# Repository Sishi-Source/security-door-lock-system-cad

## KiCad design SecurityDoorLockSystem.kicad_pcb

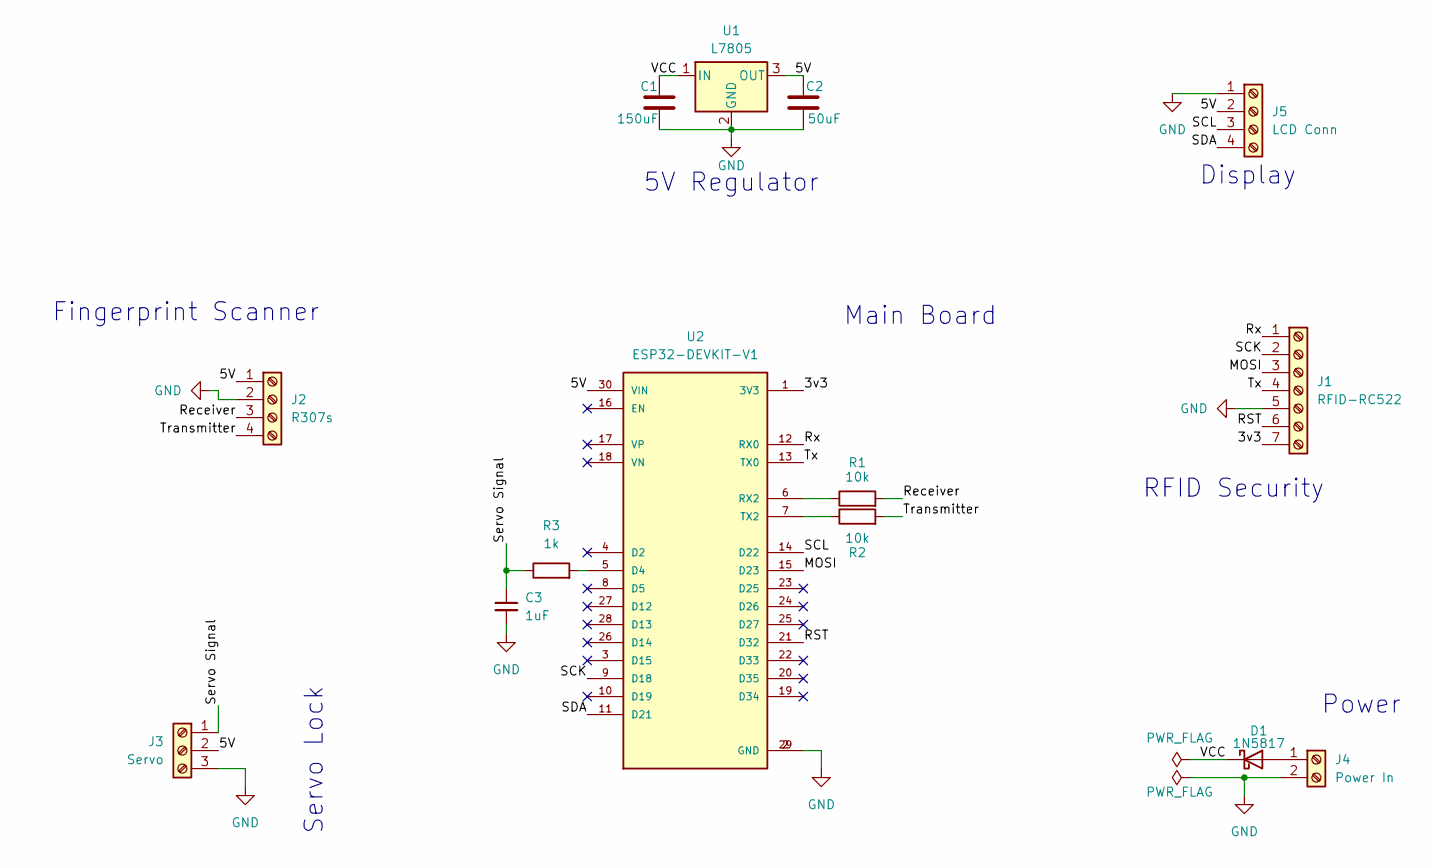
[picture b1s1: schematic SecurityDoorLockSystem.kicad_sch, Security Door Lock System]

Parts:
C1: 150uF; C_Radial_D5.0mm_H7.0mm_P2.00mm
C2: 50uF; C_Radial_D5.0mm_H7.0mm_P2.00mm
C3: 1uF; C_Radial_D5.0mm_H11.0mm_P2.00mm
D1: 1N5817; D_DO-41_SOD81_P7.62mm_Horizontal
J1: RFID-RC522; TerminalBlock_Phoenix_MKDS-1,5-7_1x07_P5.00mm_Horizontal
J2: R307s; TerminalBlock_Phoenix_MKDS-1,5-4_1x04_P5.00mm_Horizontal
J3: Servo; TerminalBlock_Phoenix_MKDS-1,5-3_1x03_P5.00mm_Horizontal
J4: Power In; TerminalBlock_Phoenix_MKDS-1,5-2_1x02_P5.00mm_Horizontal
J5: LCD Conn; TerminalBlock_Phoenix_MKDS-1,5-4_1x04_P5.00mm_Horizontal
R1, R2: 10k; R_Axial_DIN0207_L6.3mm_D2.5mm_P7.62mm_Horizontal
R3: 1k; R_Axial_DIN0207_L6.3mm_D2.5mm_P7.62mm_Horizontal
U1: L7805; TO-220-3_Horizontal_TabDown
U2: ESP32-DEVKIT-V1; MODULE_ESP32_DEVKIT_V1; PARTREV N/A

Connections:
/3v3: J1.7, U2.1 (3V3)
/5V: C2.1, J2.1, J3.2, J5.2, U1.3 (OUT), U2.30 (VIN)
/MOSI: J1.3, U2.15 (D23)
/RST: J1.6, U2.21 (D32)
/Receiver: J2.3, R1.2
/Rx: J1.1, U2.12 (RX0)
/SCK: J1.2, U2.9 (D18)
/SCL: J5.3, U2.14 (D22)
/SDA: J5.4, U2.11 (D21)
/Servo Signal: C3.1, J3.1, R3.1
/Transmitter: J2.4, R2.2
/Tx: J1.4, U2.13 (TX0)
/VCC: C1.1, D1.1 (K), U1.1 (IN)
GND: C1.2, C2.2, C3.2, J1.5, J2.2, J3.3, J4.2, J5.1, U1.2 (GND), U2.2 (GND), U2.29 (GND)
unnamed: D1.2 (A), J4.1
unnamed: R3.2, U2.5 (D4)
unnamed: R1.1, U2.6 (RX2)
unnamed: R2.1, U2.7 (TX2)

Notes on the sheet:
Power
Main Board
Display
RFID Security
Servo Lock
Fingerprint Scanner
5V Regulator

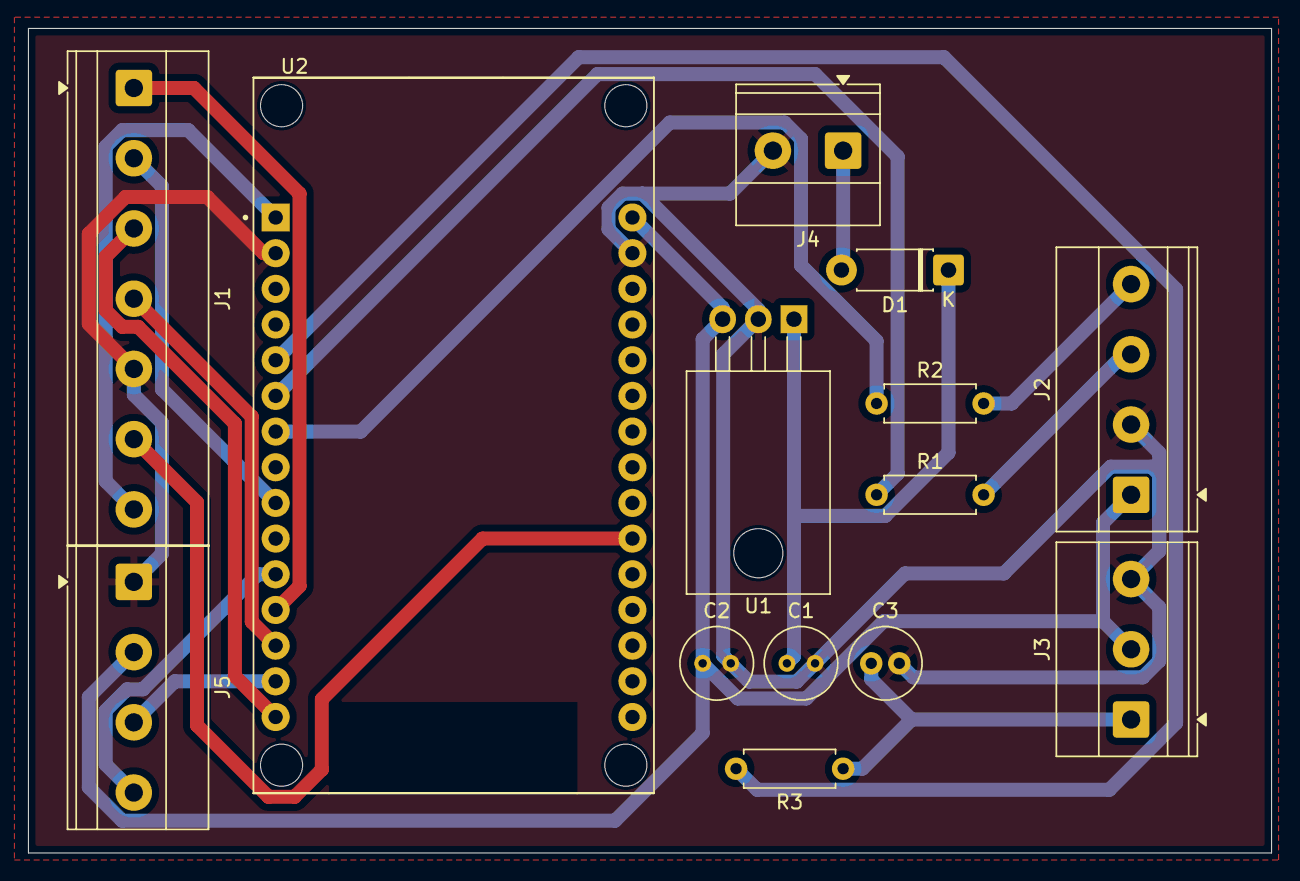
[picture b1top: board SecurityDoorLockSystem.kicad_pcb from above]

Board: 2 copper layers, 88.5 x 58.7 mm, 14 parts (0 on the bottom side), 18 nets.

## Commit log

2025-09-27 version 1
2025-09-28 version 2
    increased track width
    added voltage regulator
    corrected tht-friendly error
2025-09-28 version 2
    updated gerber plot files
    updated pdf plot files
    updated gerber/pdf drill maps files
2025-10-01 updated backup
2025-10-01 added: protection -- modified: pcb, schematic
    added power source polarity protection
    changed tracks (sizes and routes)
    changed schematic diagram connectors to screw terminals
    changed pcb connectors to screw terminals
2025-10-02 new backups
2025-10-02 board2pdf output plot
2025-10-02 modified capacitor values
    changed value of capacitors 1 and 2; C1 = 100uF, C2 = 50uF
2025-10-02 modified capacitor values
2025-10-05 new backup
2025-10-05 added front view picture of pcb
2025-10-05 added schematic diagram svg
2025-10-05 added diagram folder
2025-10-06 added lcd
2025-10-06 updated front view pic with display interface
2025-10-07 added blender 3d model
2025-10-07 cropped and upscaled pcb pic
2025-10-31 added bom
2025-10-31 added local 3d model
